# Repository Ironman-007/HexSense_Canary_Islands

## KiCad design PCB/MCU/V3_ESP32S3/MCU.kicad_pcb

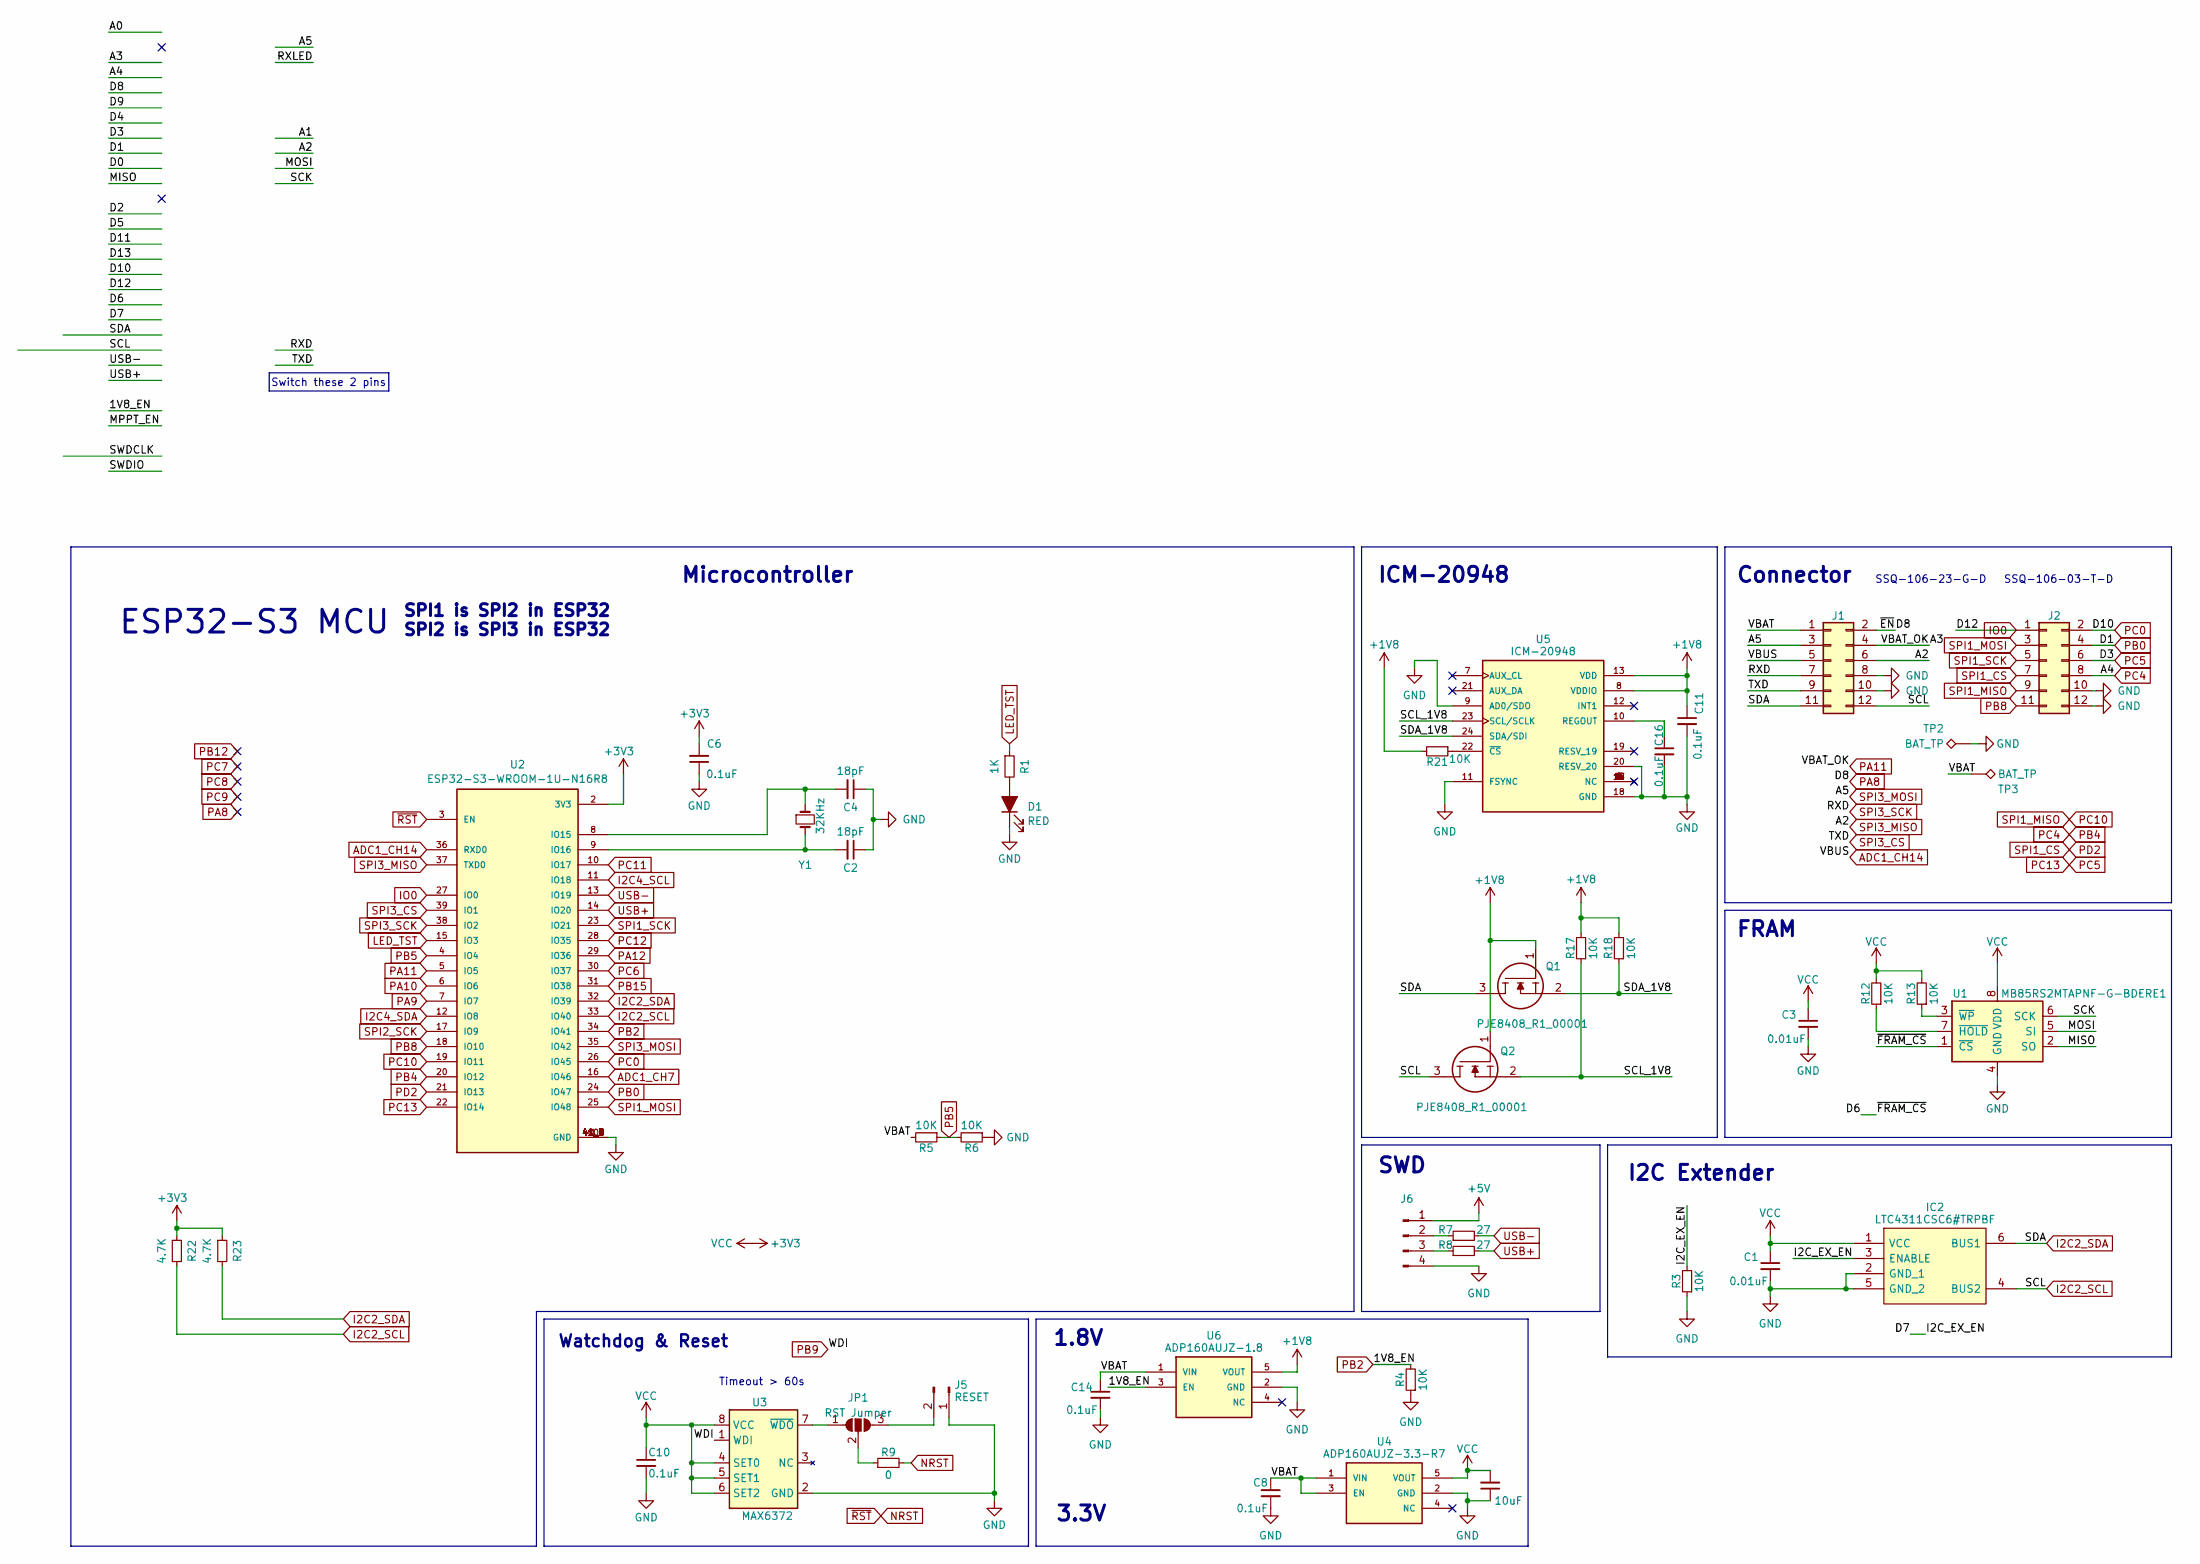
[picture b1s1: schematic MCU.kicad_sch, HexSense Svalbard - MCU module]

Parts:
C1, C3: 0.01uF; C_0402_1005Metric_Pad0.74x0.62mm_HandSolder
C2, C4: 18pF; C_0402_1005Metric_Pad0.74x0.62mm_HandSolder
C6, C8, C11, C14, C16: 0.1uF; C_0402_1005Metric_Pad0.74x0.62mm_HandSolder
C9: 10uF; C_0603_1608Metric_Pad1.08x0.95mm_HandSolder
C10: 0.1uF; C_0402_1005Metric
D1: RED; LED_0402_1005Metric_Pad0.77x0.64mm_HandSolder
IC2: LTC4311CSC6#TRPBF; SOT65P210X100-6N; Manufacturer_Part_Number LTC4311CSC6#TRPBF; Mouser Part Number 584-LTC4311CSC6TRPBF
J1, J2: Conn_02x06_Odd_Even; PinHeader_2x06_P2.54mm_Vertical
J5: RESET; PinHeader_1x02_P2.00mm_Vertical
J6: Conn_01x04_Pin; PinHeader_1x04_P2.00mm_Vertical
JP1: RST Jumper; SolderJumper-3_P1.3mm_Open_RoundedPad1.0x1.5mm
Q1, Q2: PJE8408_R1_00001; SOTFL50P160X60-3N; Manufacturer_Part_Number PJE8408_R1_00001; Mouser Part Number 241-PJE8408_R1_00001
R1: 1K; R_0402_1005Metric_Pad0.72x0.64mm_HandSolder
R3, R4, R5, R6, R12, R13, R17, R18, R21: 10K; R_0402_1005Metric_Pad0.72x0.64mm_HandSolder
R7, R8: 27; R_0402_1005Metric_Pad0.72x0.64mm_HandSolder
R9: 0; R_0201_0603Metric
R22, R23: 4.7K; R_0402_1005Metric_Pad0.72x0.64mm_HandSolder
TP2, TP3: BAT_TP; TestPoint_Pad_1.0x1.0mm
U1: MB85RS2MTAPNF-G-BDERE1; SSOP-8_5.25x5.24mm_P1.27mm
U2: ESP32-S3-WROOM-1U-N16R8; XCVR_ESP32-S3-WROOM-1U-N16R8; PARTREV v1.1
U3: MAX6372; SOT-23-8
U4: ADP160AUJZ-3.3-R7; TSOT-23-5; PARTREV H
U5: ICM-20948; InvenSense_QFN-24_3x3mm_P0.4mm; PARTREV 1.3
U6: ADP160AUJZ-1.8; TSOT-23-5; PARTREV H
Y1: 32KHz; Crystal_SMD_3215-2Pin_3.2x1.5mm

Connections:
+1V8: C11.1, Q1.1, Q2.1, R17.2, R18.2, R21.2, U5.8 (VDDIO), U5.13 (VDD), U6.5 (VOUT)
+3V3: C1.1, C3.1, C6.2, C9.2, C10.1, IC2.1 (VCC), R12.2, R13.2, R22.1, R23.1, U1.8 (VDD), U2.2 (3V3), U3.4 (SET0), U3.5 (SET1), U3.6 (SET2), U3.8 (VCC), U4.5 (VOUT)
+5V: J6.1
/D6: U1.1 (~CS)
/D7: IC2.3 (ENABLE), R3.2
/MISO: U1.2 (SO)
/MOSI: U1.5 (SI)
/SCK: U1.6 (SCK)
/SCL_1V8: Q2.2, R17.1, U5.23 (SCL/SCLK)
/SDA_1V8: Q1.2, R18.1, U5.24 (SDA/SDI)
/VBAT: C8.1, C14.1, J1.1, R5.2, TP3.1, U4.1 (VIN), U4.3 (EN), U6.1 (VIN)
ADC1_CH7: U2.16 (IO46)
ADC1_CH14: J1.5, U2.36 (RXD0)
GND: C1.2, C2.1, C3.2, C4.1, C6.1, C8.2, C9.1, C10.2, C11.2, C14.2, C16.2, D1.1 (K), IC2.2 (GND_1), IC2.5 (GND_2), J1.8, J1.10, J2.10, J2.12, J5.1, J6.4, R3.1, R4.1, R6.1, TP2.1, U1.4 (GND), U2.1 (GND), U2.40 (GND), U2.41_1 (GND), U2.41_2 (GND), U2.41_3 (GND), U2.41_4 (GND), U2.41_5 (GND), U2.41_6 (GND), U2.41_7 (GND), U2.41_8 (GND), U2.41_9 (GND), U3.2 (GND), U4.2 (GND), U5.9 (AD0/SDO), U5.11 (FSYNC), U5.18 (GND), U5.20 (RESV_20), U6.2 (GND)
I2C2_SCL: IC2.4 (BUS2), J1.12, Q2.3, R22.2, U2.33 (IO40)
I2C2_SDA: IC2.6 (BUS1), J1.11, Q1.3, R23.2, U2.32 (IO39)
I2C4_SCL: U2.11 (IO18)
I2C4_SDA: U2.12 (IO8)
IO0: J2.1, U2.27 (IO0)
LED_TST: R1.1, U2.15 (IO3)
NRST: R9.2, U2.3 (EN)
unnamed: D1.2 (A), R1.2
unnamed: J5.2, JP1.3 (B)
unnamed: J6.2, R7.1
unnamed: J6.3, R8.1
unnamed: JP1.1 (A), U3.7 (~WDO)
unnamed: JP1.2 (C), R9.1
unnamed: R12.1, U1.7 (~HOLD)
unnamed: R13.1, U1.3 (~WP)
unnamed: C4.2, U2.8 (IO15), Y1.1
unnamed: C2.2, U2.9 (IO16), Y1.2
unnamed: C16.1, U5.10 (REGOUT)
unnamed: R21.1, U5.22 (~CS)
PA8: J1.2
PA9: U2.7 (IO7)
PA10: U2.6 (IO6)
PA11: J1.4, U2.5 (IO5)
PA12: U2.29 (IO36)
PB0: J2.4, U2.24 (IO47)
PB2: R4.2, U2.34 (IO41), U6.3 (EN)
PB4: J2.8, U2.20 (IO12)
PB5: R5.1, R6.2, U2.4 (IO4)
PB8: J2.11, U2.18 (IO10)
PB9: U3.1 (WDI)
PB15: U2.31 (IO38)
PC0: J2.2, U2.26 (IO45)
PC6: U2.30 (IO37)
PC10: J2.9, U2.19 (IO11)
PC11: U2.10 (IO17)
PC12: U2.28 (IO35)
PC13: J2.6, U2.22 (IO14)
PD2: J2.7, U2.21 (IO13)
SPI1_MOSI: J2.3, U2.25 (IO48)
SPI1_SCK: J2.5, U2.23 (IO21)
SPI2_SCK: U2.17 (IO9)
SPI3_CS: J1.9, U2.39 (IO1)
SPI3_MISO: J1.6, U2.37 (TXD0)
SPI3_MOSI: J1.3, U2.35 (IO42)
SPI3_SCK: J1.7, U2.38 (IO2)
USB+: R8.2, U2.14 (IO20)
USB-: R7.2, U2.13 (IO19)

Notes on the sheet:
ICM-20948
SSQ-106-03-T-D
1.8V
SPI1 is SPI2 in ESP32 SPI2 is SPI3 in ESP32
Microcontroller
FRAM
Timeout > 60s
ESP32-S3 MCU
Watchdog & Reset
SWD
Connector
3.3V
Switch these 2 pins
SSQ-106-23-G-D
I2C Extender

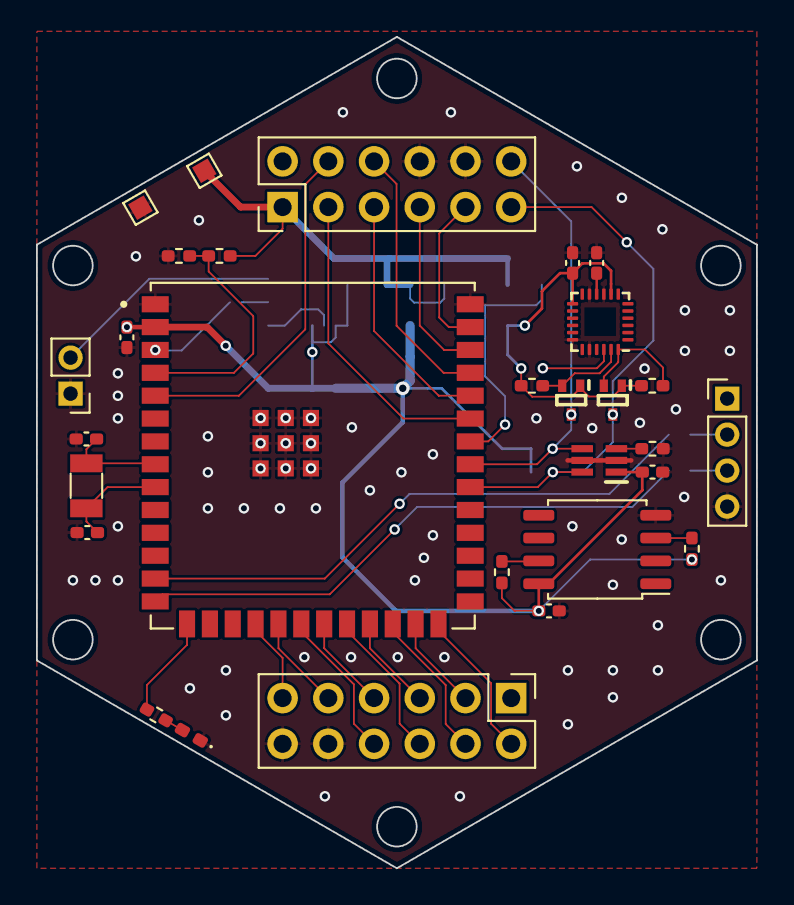
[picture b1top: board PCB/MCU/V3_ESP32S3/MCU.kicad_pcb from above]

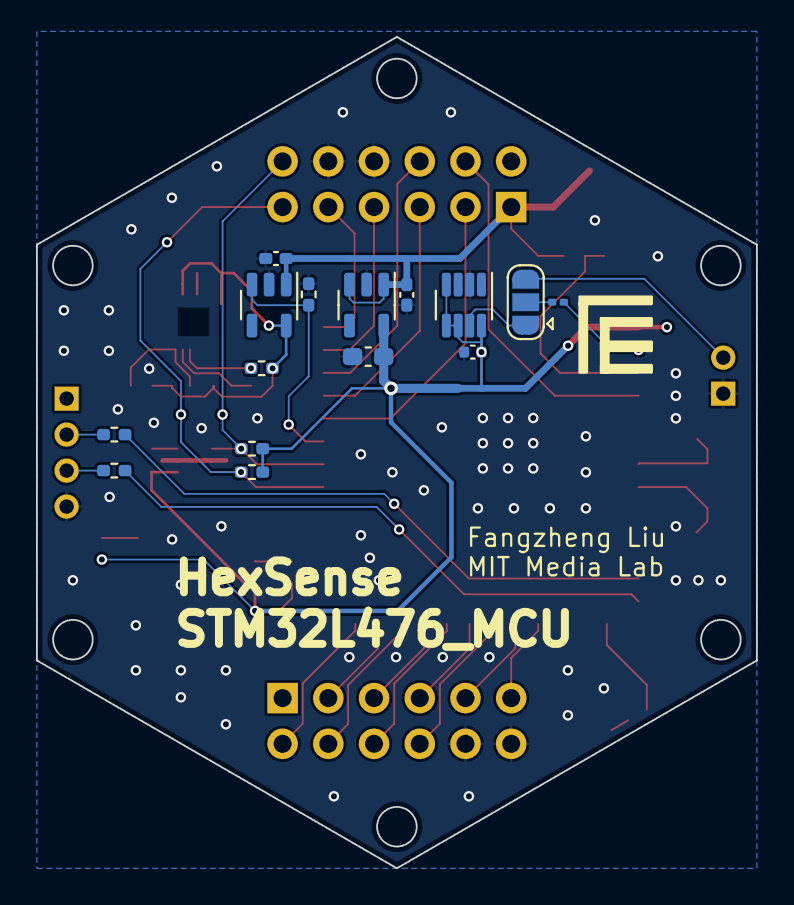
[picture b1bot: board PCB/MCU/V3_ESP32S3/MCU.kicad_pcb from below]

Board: 2 copper layers, 40.0 x 46.2 mm, 44 parts (15 on the bottom side), 43 nets.

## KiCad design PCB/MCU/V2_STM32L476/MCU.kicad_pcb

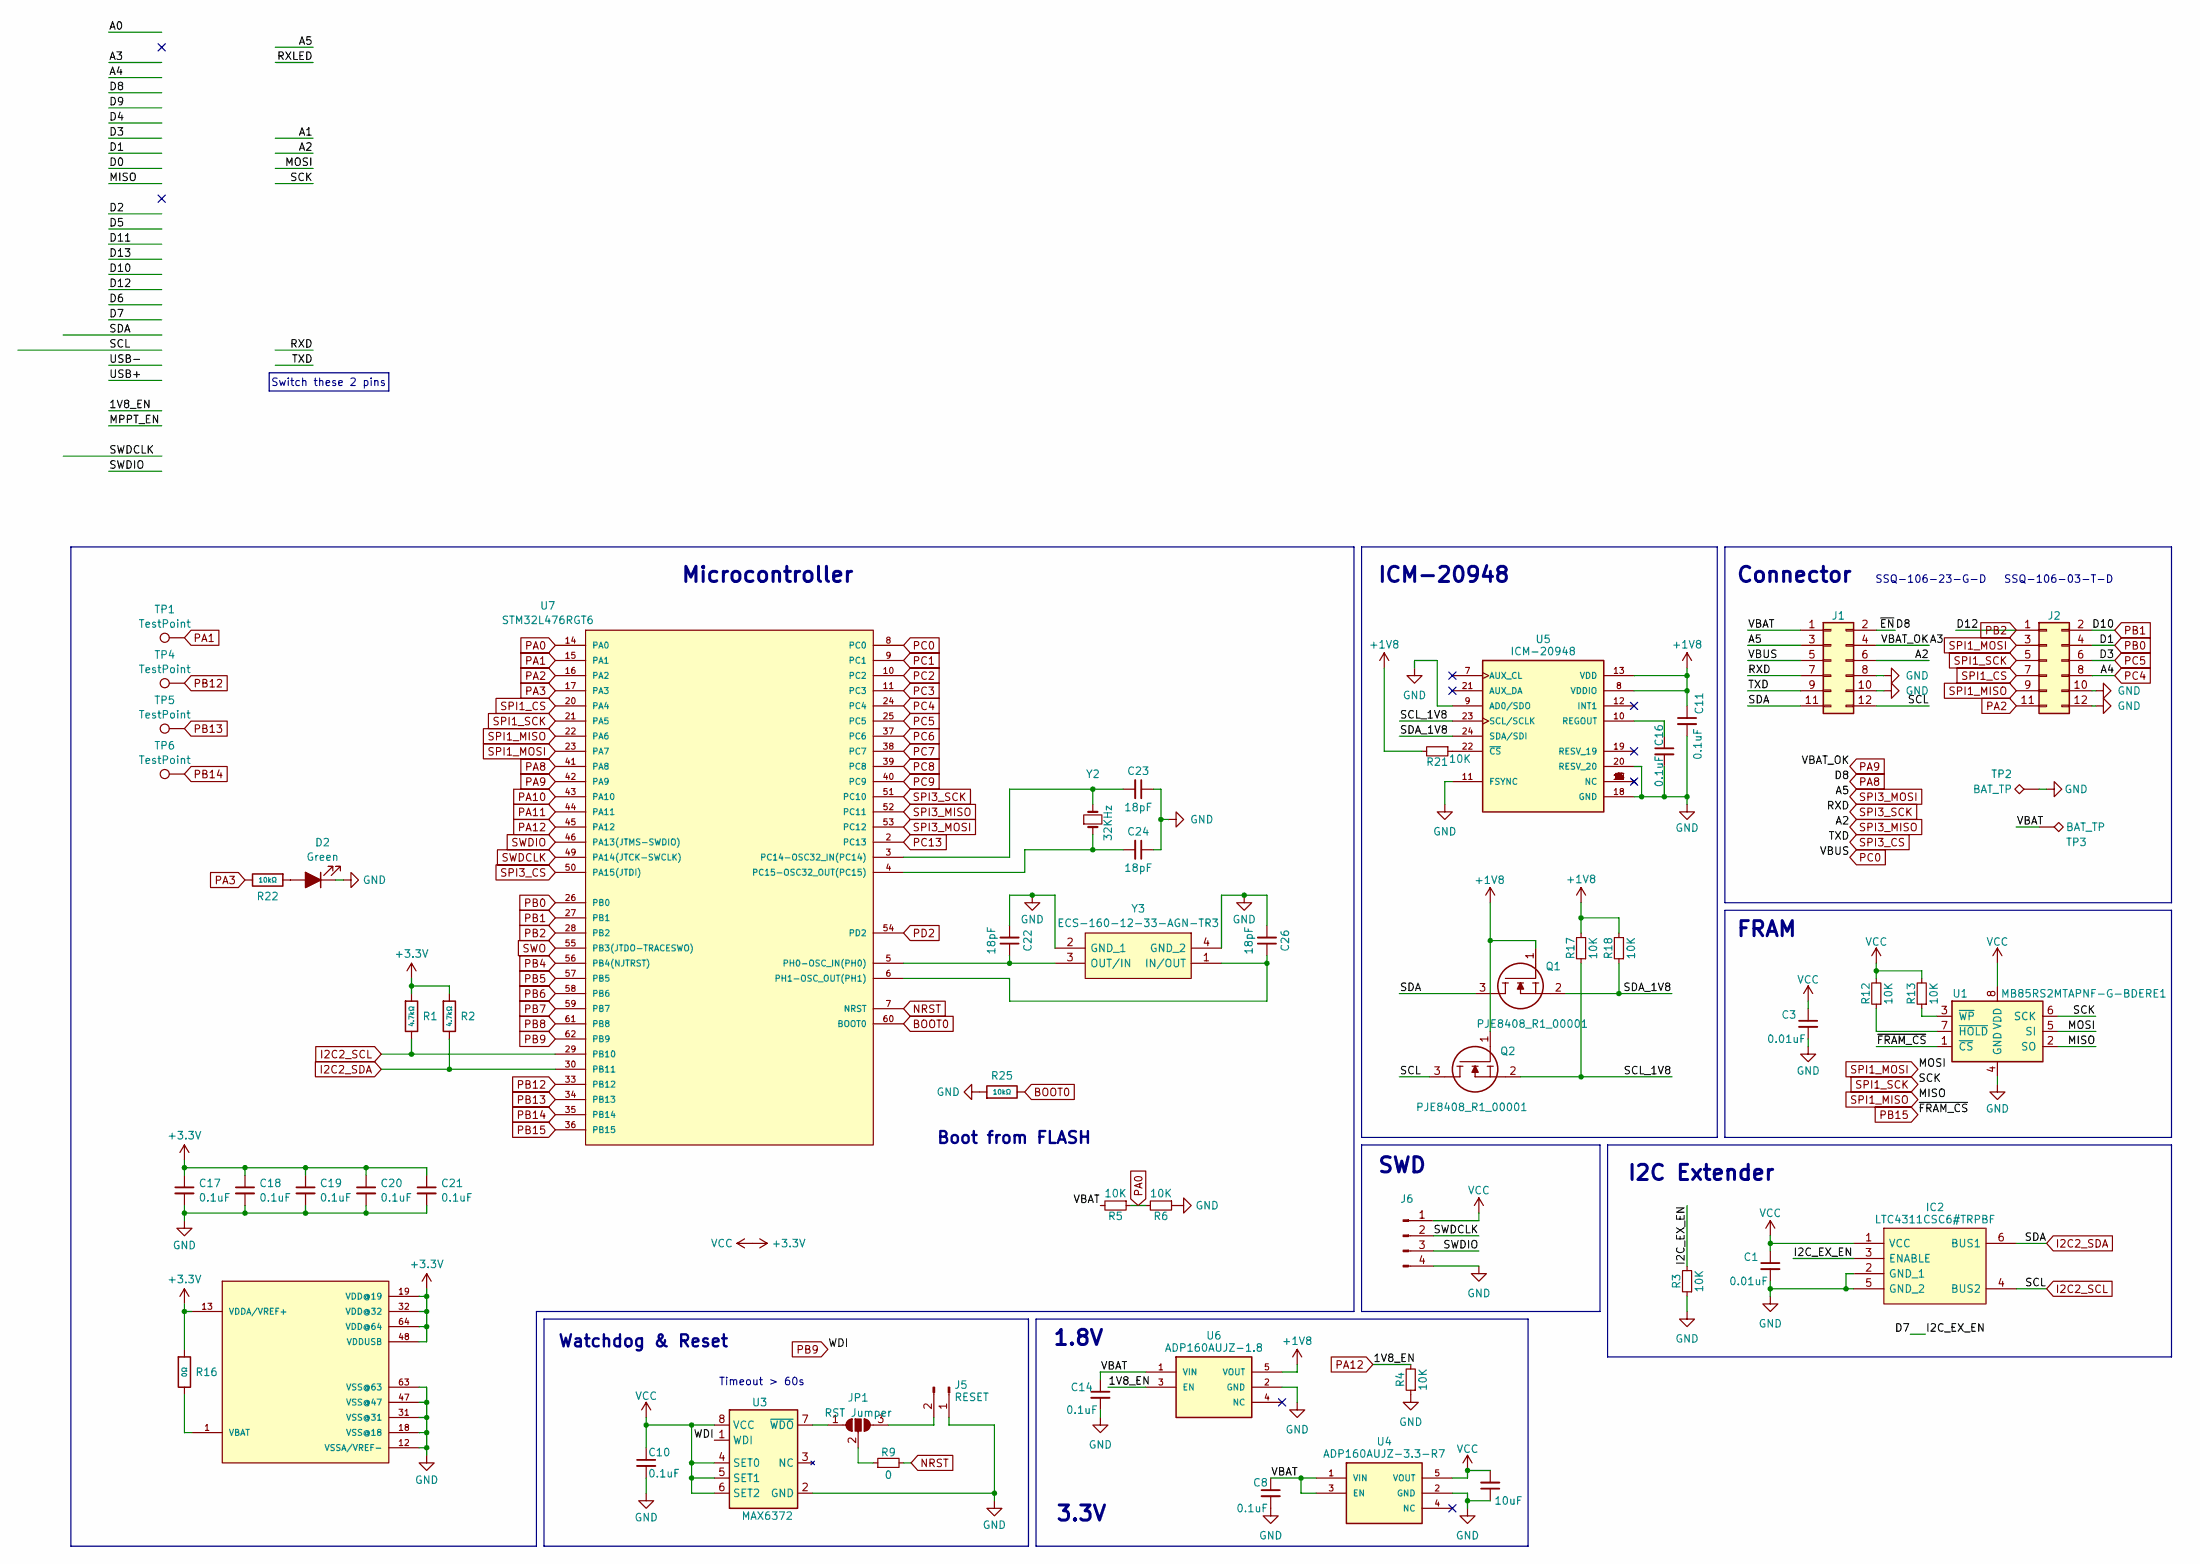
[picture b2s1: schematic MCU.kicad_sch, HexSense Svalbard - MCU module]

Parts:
C1, C3: 0.01uF; C_0402_1005Metric_Pad0.74x0.62mm_HandSolder
C8, C11, C14, C16, C17, C18, C19, C20, C21: 0.1uF; C_0402_1005Metric_Pad0.74x0.62mm_HandSolder
C9: 10uF; C_0603_1608Metric_Pad1.08x0.95mm_HandSolder
C10: 0.1uF; C_0402_1005Metric
C22, C23, C24, C26: 18pF; C_0402_1005Metric_Pad0.74x0.62mm_HandSolder
D2: Green; LED_0402_1005Metric_Pad0.77x0.64mm_HandSolder
IC2: LTC4311CSC6#TRPBF; SOT65P210X100-6N; Manufacturer_Part_Number LTC4311CSC6#TRPBF; Mouser Part Number 584-LTC4311CSC6TRPBF
J1, J2: Conn_02x06_Odd_Even; PinHeader_2x06_P2.54mm_Vertical
J5: RESET; PinHeader_1x02_P2.00mm_Vertical
J6: Conn_01x04_Pin; PinHeader_1x04_P2.00mm_Vertical
JP1: RST Jumper; SolderJumper-3_P1.3mm_Open_RoundedPad1.0x1.5mm
Q1, Q2: PJE8408_R1_00001; SOTFL50P160X60-3N; Manufacturer_Part_Number PJE8408_R1_00001; Mouser Part Number 241-PJE8408_R1_00001
R1, R2: 4.7kΩ; R_0402; Overload Voltage (Max) 50V; Tolerance ±1%; Part 0402WGF4701TCE; LCSC C25900
R3, R4, R5, R6, R12, R13, R17, R18, R21: 10K; R_0402_1005Metric_Pad0.72x0.64mm_HandSolder
R9: 0; R_0201_0603Metric
R16: 0Ω; R_0402; Overload Voltage (Max) 50V; Tolerance ±1%; Part 0402WGF0000TCE; LCSC C17168
R22: 10kΩ; R_0402_1005Metric_Pad0.72x0.64mm_HandSolder; Overload Voltage (Max) 75V; Tolerance ±1%; Part 0603WAF1001T5E; LCSC C21190
R25: 10kΩ; R_0603_1608Metric_Pad0.98x0.95mm_HandSolder; Overload Voltage (Max) 200V; Tolerance ±1%; Part 1206W4F1002T5E; LCSC C17902
TP1, TP4, TP5, TP6: TestPoint; TestPoint_Pad_D1.0mm
TP2, TP3: BAT_TP; TestPoint_Pad_1.0x1.0mm
U1: MB85RS2MTAPNF-G-BDERE1; SSOP-8_5.25x5.24mm_P1.27mm
U3: MAX6372; SOT-23-8
U4: ADP160AUJZ-3.3-R7; TSOT-23-5; PARTREV H
U5: ICM-20948; InvenSense_QFN-24_3x3mm_P0.4mm; PARTREV 1.3
U6: ADP160AUJZ-1.8; TSOT-23-5; PARTREV H
U7: STM32L476RGT6; LQFP-64_10x10mm_P0.5mm
Y2: 32KHz; Crystal_SMD_3215-2Pin_3.2x1.5mm
Y3: ECS-160-12-33-AGN-TR3; XTAL_ECS-160-12-33-AGN-TR3; Manufacturer_Part_Number ECS-160-12-33-AGN-TR3; Mouser Part Number 520-160-12-33AGN-TR3

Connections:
+1V8: C11.1, Q1.1, Q2.1, R17.2, R18.2, R21.2, U5.8 (VDDIO), U5.13 (VDD), U6.5 (VOUT)
+3.3V: C1.1, C3.1, C9.2, C10.1, C17.1, C18.1, C19.1, C20.1, C21.1, IC2.1 (VCC), J6.1, R1.1, R2.1, R12.2, R13.2, R16.1, U1.8 (VDD), U3.4 (SET0), U3.5 (SET1), U3.6 (SET2), U3.8 (VCC), U4.5 (VOUT), U7.13 (VDDA/VREF+), U7.19 (VDD@19), U7.32 (VDD@32), U7.48 (VDDUSB), U7.64 (VDD@64)
/D7: IC2.3 (ENABLE), R3.2
/SCL_1V8: Q2.2, R17.1, U5.23 (SCL/SCLK)
/SDA_1V8: Q1.2, R18.1, U5.24 (SDA/SDI)
/VBAT: C8.1, C14.1, J1.1, R5.2, TP3.1, U4.1 (VIN), U4.3 (EN), U6.1 (VIN)
BOOT0: R25.2, U7.60 (BOOT0)
GND: C1.2, C3.2, C8.2, C9.1, C10.2, C11.2, C14.2, C16.2, C17.2, C18.2, C19.2, C20.2, C21.2, C22.2, C23.1, C24.1, C26.2, D2.1 (K), IC2.2 (GND_1), IC2.5 (GND_2), J1.8, J1.10, J2.10, J2.12, J5.1, J6.4, R3.1, R4.1, R6.1, R25.1, TP2.1, U1.4 (GND), U3.2 (GND), U4.2 (GND), U5.9 (AD0/SDO), U5.11 (FSYNC), U5.18 (GND), U5.20 (RESV_20), U6.2 (GND), U7.12 (VSSA/VREF-), U7.18 (VSS@18), U7.31 (VSS@31), U7.47 (VSS@47), U7.63 (VSS@63), Y3.2 (GND_1), Y3.4 (GND_2)
I2C2_SCL: IC2.4 (BUS2), J1.12, Q2.3, R1.2, U7.29 (PB10)
I2C2_SDA: IC2.6 (BUS1), J1.11, Q1.3, R2.2, U7.30 (PB11)
NRST: R9.2, U7.7 (NRST)
unnamed: D2.2 (A), R22.1
unnamed: J5.2, JP1.3 (B)
unnamed: JP1.1 (A), U3.7 (~WDO)
unnamed: JP1.2 (C), R9.1
unnamed: R12.1, U1.7 (~HOLD)
unnamed: R13.1, U1.3 (~WP)
unnamed: C16.1, U5.10 (REGOUT)
unnamed: R21.1, U5.22 (~CS)
unnamed: C23.2, U7.3 (PC14-OSC32_IN(PC14)), Y2.2
unnamed: C24.2, U7.4 (PC15-OSC32_OUT(PC15)), Y2.1
unnamed: C22.1, U7.5 (PH0-OSC_IN(PH0)), Y3.3 (OUT/IN)
unnamed: C26.1, U7.6 (PH1-OSC_OUT(PH1)), Y3.1 (IN/OUT)
unnamed: R16.2, U7.1 (VBAT)
PA0: R5.1, R6.2, U7.14 (PA0)
PA1: TP1.1, U7.15 (PA1)
PA2: J2.11, U7.16 (PA2)
PA3: R22.2, U7.17 (PA3)
PA8: J1.2, U7.41 (PA8)
PA9: J1.4, U7.42 (PA9)
PA10: U7.43 (PA10)
PA11: U7.44 (PA11)
PA12: R4.2, U6.3 (EN), U7.45 (PA12)
PB0: J2.4, U7.26 (PB0)
PB1: J2.2, U7.27 (PB1)
PB2: J2.1, U7.28 (PB2)
PB4: U7.56 (PB4(NJTRST))
PB5: U7.57 (PB5)
PB6: U7.58 (PB6)
PB7: U7.59 (PB7)
PB8: U7.61 (PB8)
PB9: U3.1 (WDI), U7.62 (PB9)
PB12: TP4.1, U7.33 (PB12)
PB13: TP5.1, U7.34 (PB13)
PB14: TP6.1, U7.35 (PB14)
PB15: U1.1 (~CS), U7.36 (PB15)
PC0: J1.5, U7.8 (PC0)
PC1: U7.9 (PC1)
PC2: U7.10 (PC2)
PC3: U7.11 (PC3)
PC4: J2.8, U7.24 (PC4)
PC5: J2.6, U7.25 (PC5)
PC6: U7.37 (PC6)
PC7: U7.38 (PC7)
PC8: U7.39 (PC8)
PC9: U7.40 (PC9)
PC13: U7.2 (PC13)
PD2: U7.54 (PD2)
SPI1_CS: J2.7, U7.20 (PA4)
SPI1_MISO: J2.9, U1.2 (SO), U7.22 (PA6)
SPI1_MOSI: J2.3, U1.5 (SI), U7.23 (PA7)
SPI1_SCK: J2.5, U1.6 (SCK), U7.21 (PA5)
SPI3_CS: J1.9, U7.50 (PA15(JTDI))
SPI3_MISO: J1.6, U7.52 (PC11)
SPI3_MOSI: J1.3, U7.53 (PC12)
SPI3_SCK: J1.7, U7.51 (PC10)
SWDCLK: J6.2, U7.49 (PA14(JTCK-SWCLK))
SWDIO: J6.3, U7.46 (PA13(JTMS-SWDIO))
SWO: U7.55 (PB3(JTDO-TRACESWO))

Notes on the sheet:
ICM-20948
SSQ-106-03-T-D
1.8V
Microcontroller
FRAM
Timeout > 60s
Watchdog & Reset
SWD
Connector
3.3V
Boot from FLASH
Switch these 2 pins
SSQ-106-23-G-D
I2C Extender

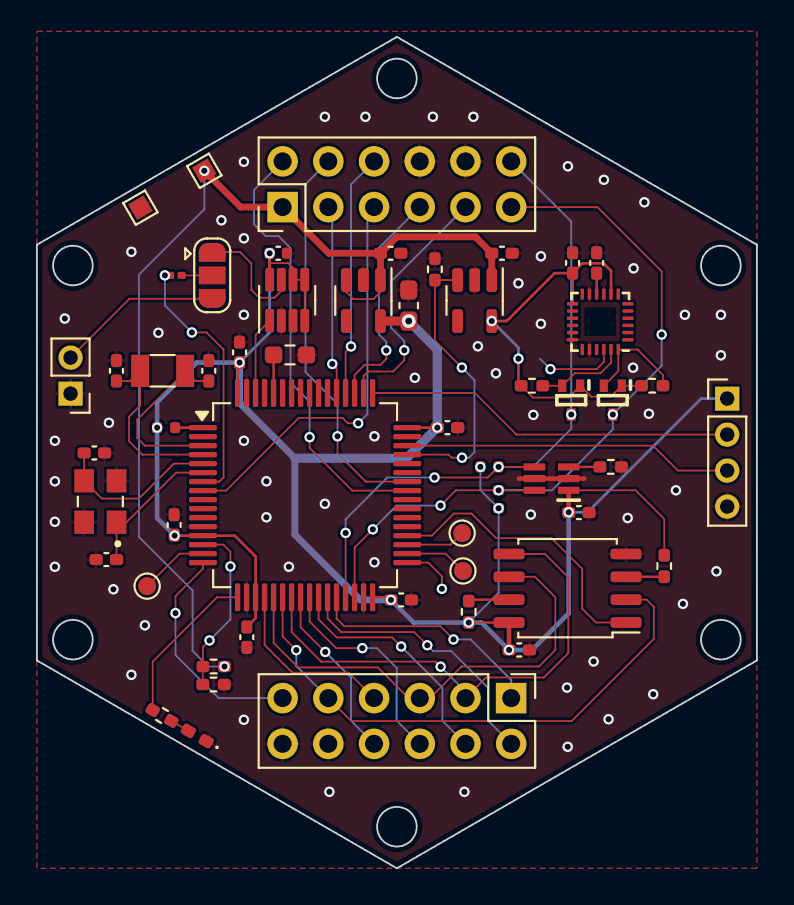
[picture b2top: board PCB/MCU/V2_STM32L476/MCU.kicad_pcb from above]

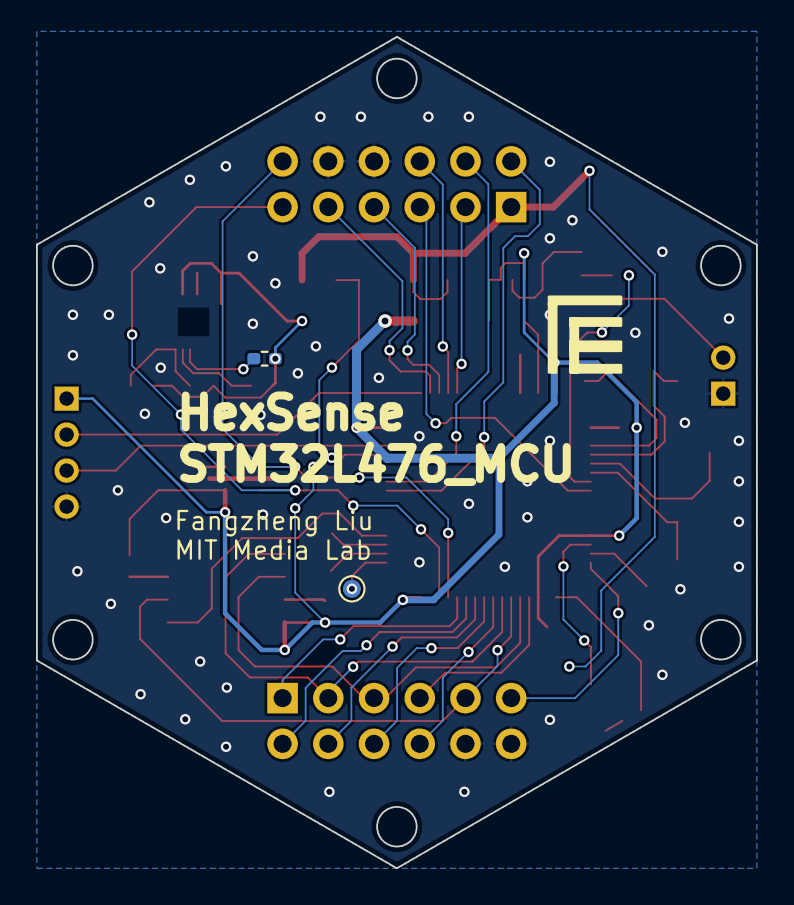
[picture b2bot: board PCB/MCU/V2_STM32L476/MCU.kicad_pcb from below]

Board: 2 copper layers, 40.0 x 46.2 mm, 55 parts (2 on the bottom side), 52 nets.

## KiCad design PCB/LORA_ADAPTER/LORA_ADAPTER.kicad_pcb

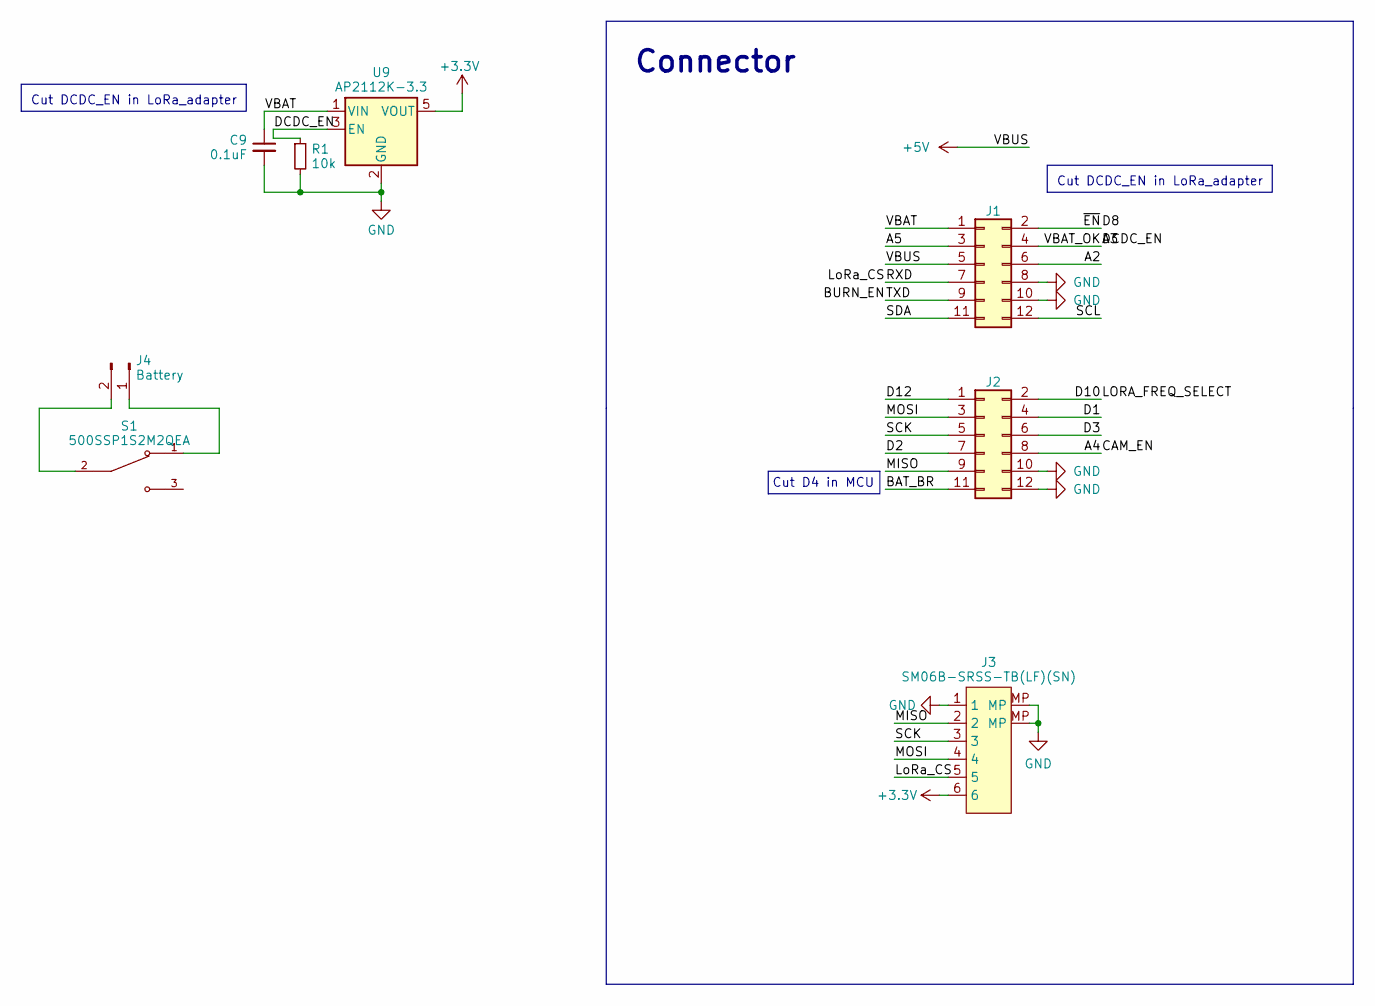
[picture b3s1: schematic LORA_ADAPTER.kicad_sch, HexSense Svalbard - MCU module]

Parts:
C9: 0.1uF; C_0402_1005Metric_Pad0.74x0.62mm_HandSolder
J1, J2: Conn_02x06_Odd_Even; PinHeader_2x06_P2.54mm_Vertical
J3: SM06B-SRSS-TB(LF)(SN); JST_SH_SM06B-SRSS-TB_1x06-1MP_P1.00mm_Horizontal
J4: Battery; PinHeader_1x02_P2.54mm_Vertical
R1: 10k; R_0402_1005Metric_Pad0.72x0.64mm_HandSolder
S1: 500SSP1S2M2QEA; SW_500SSP1S2M2QEA; PARTREV C
U9: AP2112K-3.3; SOT-23-5

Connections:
+3V3: J3.6, U9.5 (VOUT)
+5V: J1.5
/A2: J1.6
/A3: J1.4, R1.1, U9.3 (EN)
/A4: J2.8
/A5: J1.3
/BAT_BR: J2.11
/BURN_EN: J1.9
/D1: J2.4
/D2: J2.7
/D3: J2.6
/D8: J1.2
/D10: J2.2
/D12: J2.1
/LoRa_CS: J1.7, J3.5
/MISO: J2.9, J3.2
/MOSI: J2.3, J3.4
/SCK: J2.5, J3.3
/SCL: J1.12
/SDA: J1.11
/VBAT: C9.1, J1.1, U9.1 (VIN)
GND: C9.2, J1.8, J1.10, J2.10, J2.12, J3.1, J3.MP, R1.2, U9.2 (GND)
unnamed: J4.1, S1.1
unnamed: J4.2, S1.2

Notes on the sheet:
Cut D4 in MCU
Connector
Cut DCDC_EN in LoRa_adapter

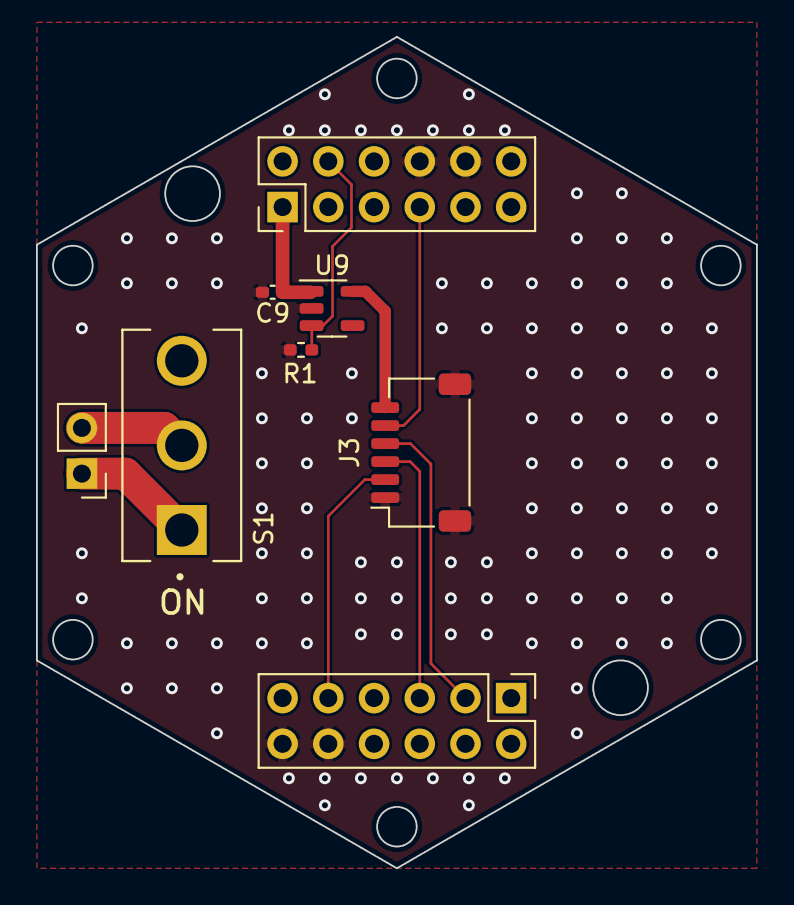
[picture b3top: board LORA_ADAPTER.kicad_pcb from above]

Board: 2 copper layers, 40.0 x 46.2 mm, 8 parts (0 on the bottom side), 10 nets.

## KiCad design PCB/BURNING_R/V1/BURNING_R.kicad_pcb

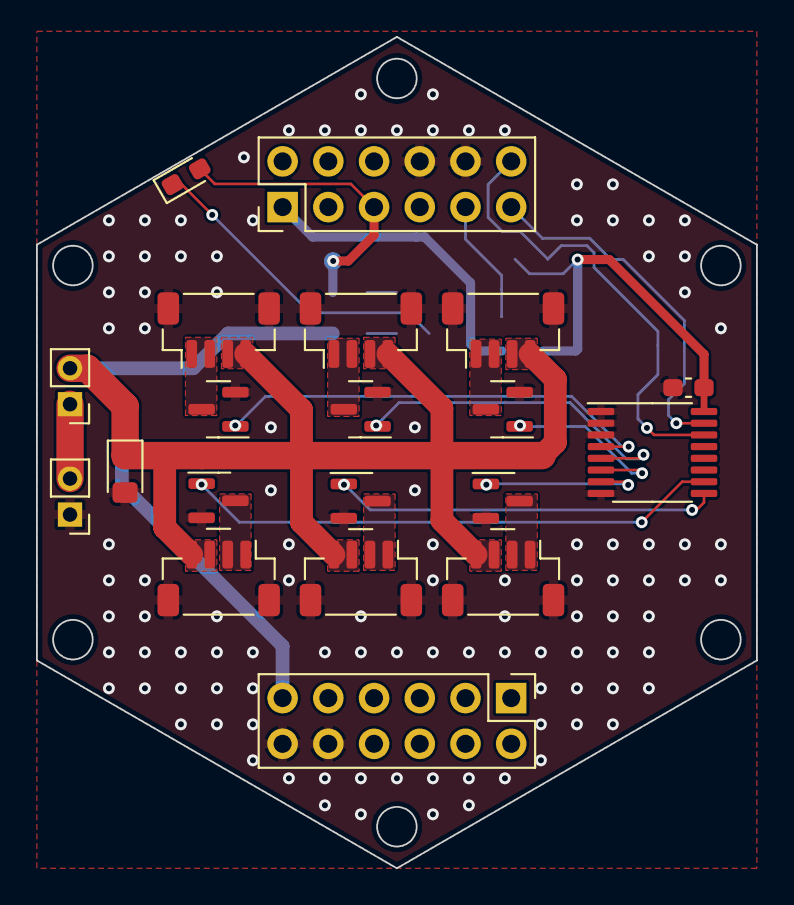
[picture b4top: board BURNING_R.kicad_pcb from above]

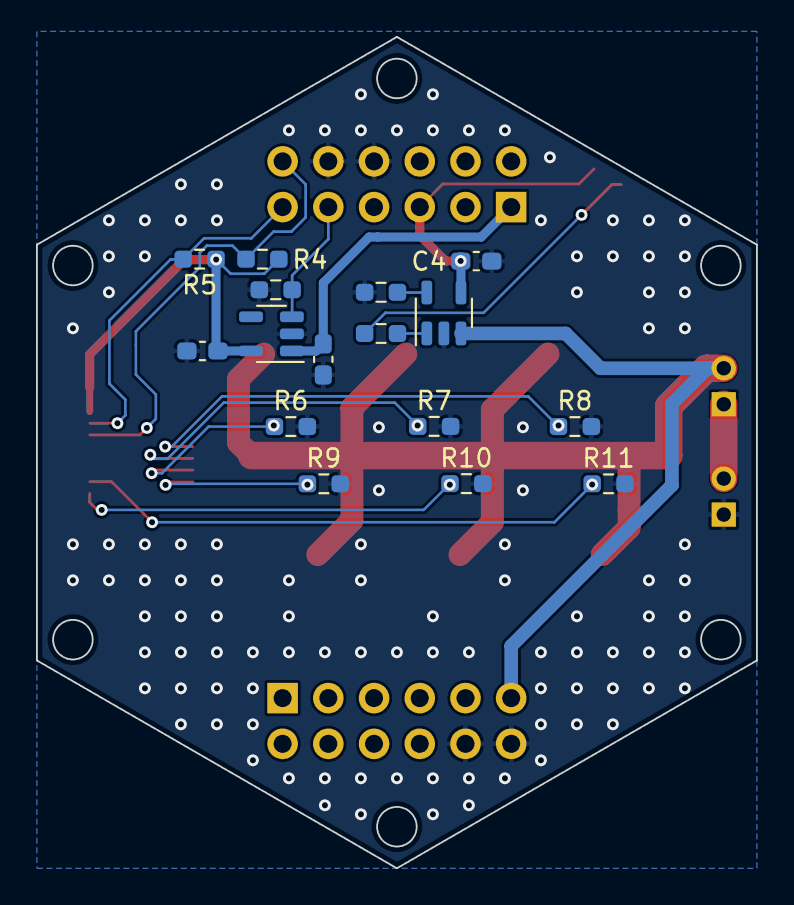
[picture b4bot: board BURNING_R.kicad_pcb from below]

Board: 2 copper layers, 40.0 x 46.2 mm, 36 parts (16 on the bottom side), 24 nets.

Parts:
C2, C4, C6: 0.1uF; C_0603_1608Metric_Pad1.08x0.95mm_HandSolder
C3: 47uF; LED_0805_2012Metric_Pad1.15x1.40mm_HandSolder
C5: 10uF; C_0603_1608Metric_Pad1.08x0.95mm_HandSolder
D1: RED; LED_0603_1608Metric_Pad1.05x0.95mm_HandSolder
J1, J2: Conn_02x06_Odd_Even; PinHeader_2x06_P2.54mm_Vertical
J3, J4, J5, J6, J7, J8: BR_conn; JST_SH_BM04B-SRSS-TB_1x04-1MP_P1.00mm_Vertical
J9: Battery; PinHeader_1x02_P2.00mm_Vertical
J10: Switch; PinHeader_1x02_P2.00mm_Vertical
Q1, Q2, Q3, Q4, Q5, Q6: DMN2056U; SOT-23
R1, R2, R3: 1k; R_0603_1608Metric_Pad0.98x0.95mm_HandSolder
R4, R5: NC; R_0603_1608Metric_Pad0.98x0.95mm_HandSolder
R6, R7, R8, R9, R10, R11: 10k; R_0603_1608Metric_Pad0.98x0.95mm_HandSolder
U1: TCA9534; TSSOP-16_4.4x5mm_P0.65mm
U2: MCP73831-2-OT; SOT-23-5
U3: ADP160AUJZ-3.3-R7; TSOT-23-5

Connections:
+5V: C4.1, D1.2 (A), J1.5, U2.4 (VDD)
/BAT_BR: C3.1, J2.11, J3.3, J3.4, J4.3, J4.4, J5.3, J5.4, J6.3, J6.4, J7.3, J7.4, J8.3, J8.4, J9.2, U2.3 (VBAT)
/BR_1: J3.1, J3.2, Q1.3 (D)
/BR_1_EN: Q1.1 (G), R11.1, U1.10 (P5)
/BR_2: J4.1, J4.2, Q2.3 (D)
/BR_2_EN: Q2.1 (G), R10.1, U1.9 (P4)
/BR_3: J5.1, J5.2, Q3.3 (D)
/BR_3_EN: Q3.1 (G), R9.1, U1.7 (P3)
/BR_4: J6.1, J6.2, Q4.3 (D)
/BR_4_EN: Q4.1 (G), R8.1, U1.4 (P0)
/BR_5: J7.1, J7.2, Q5.3 (D)
/BR_5_EN: Q5.1 (G), R7.1, U1.5 (P1)
/BR_6: J8.1, J8.2, Q6.3 (D)
/BR_6_EN: Q6.1 (G), R6.1, U1.6 (P2)
/BURN_EN: J1.9, R3.2, U3.3 (EN)
/SCL: J1.12, R4.2, U1.14 (SCL)
/SDA: J1.11, R5.2, U1.15 (SDA)
/VBAT: C6.1, J1.1, U3.1 (VIN)
GND: C2.2, C3.2, C4.2, C5.1, C6.2, J1.8, J1.10, J2.10, J2.12, J3.MP, J4.MP, J5.MP, J6.MP, J7.MP, J8.MP, J10.1, Q1.2 (S), Q2.2 (S), Q3.2 (S), Q4.2 (S), Q5.2 (S), Q6.2 (S), R1.1, R3.1, R6.2, R7.2, R8.2, R9.2, R10.2, R11.2, U1.1 (A0), U1.2 (A1), U1.3 (A2), U1.8 (GND), U2.2 (VSS), U3.2 (GND)
unnamed: D1.1 (K), R2.2
unnamed: J9.1, J10.2
unnamed: R1.2, U2.5 (PROG)
unnamed: R2.1, U2.1 (STAT)
VCC: C2.1, C5.2, R4.1, R5.1, U1.16 (VDD), U3.5 (VOUT)

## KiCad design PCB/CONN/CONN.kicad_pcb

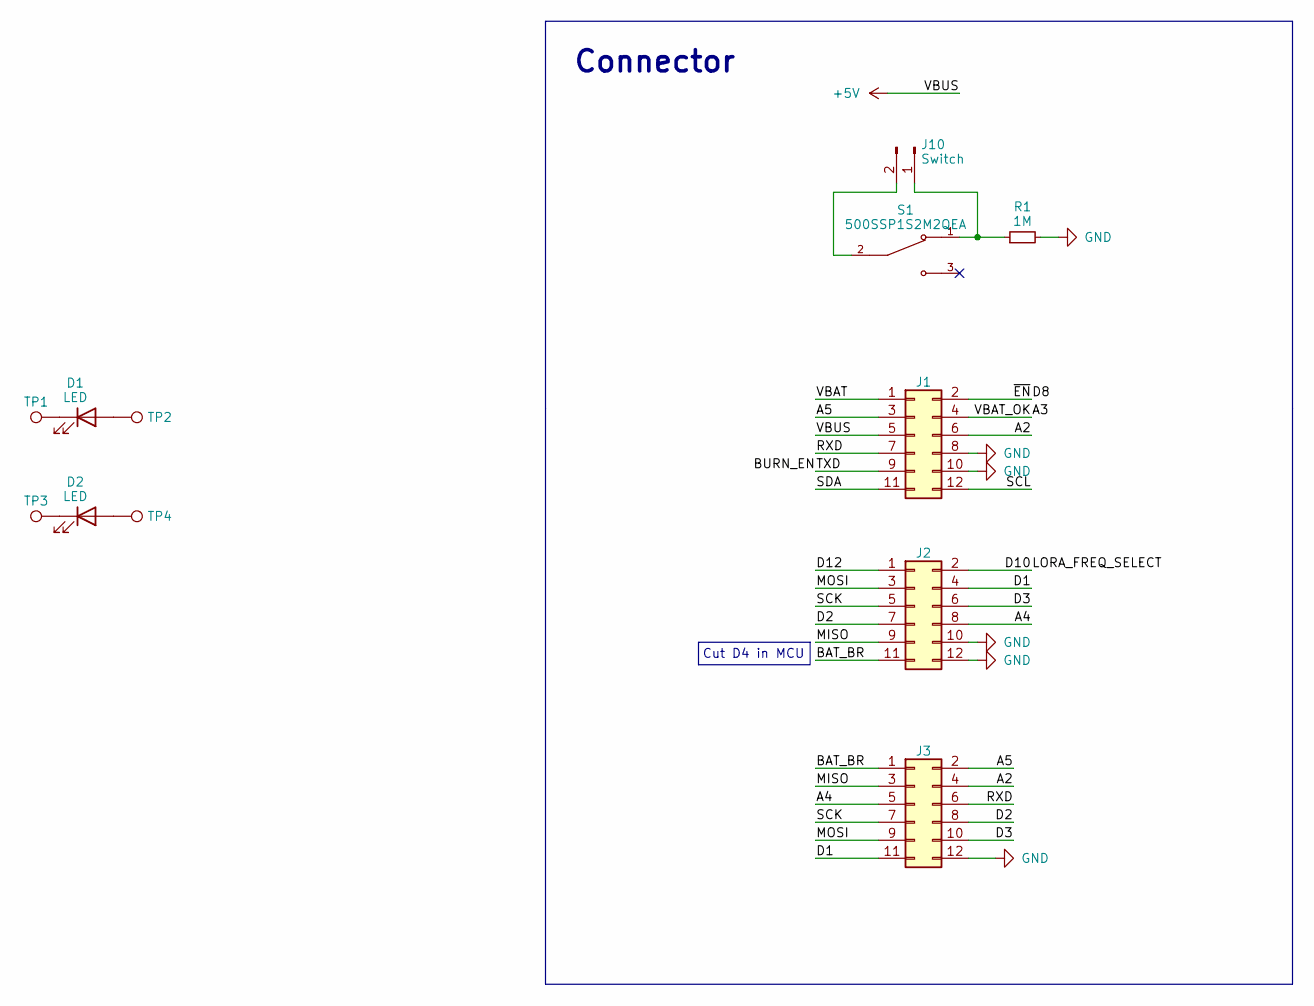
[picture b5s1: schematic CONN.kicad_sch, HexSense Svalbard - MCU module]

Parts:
D1, D2: LED; LED_1206_3216Metric_Pad1.42x1.75mm_HandSolder
J1, J2, J3: Conn_02x06_Odd_Even; PinHeader_2x06_P2.54mm_Vertical
J10: Switch; PinHeader_1x02_P2.00mm_Vertical
R1: 1M; R_0603_1608Metric_Pad0.98x0.95mm_HandSolder
S1: 500SSP1S2M2QEA; SW_500SSP1S2M2QEA; PARTREV C
TP1, TP2, TP3, TP4: TestPoint; TestPoint_Pad_1.0x1.0mm

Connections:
+5V: J1.5
/A2: J1.6, J3.4
/A3: J1.4
/A4: J2.8, J3.5
/A5: J1.3, J3.2
/BAT_BR: J2.11, J3.1
/BURN_EN: J1.9
/D1: J2.4, J3.11
/D2: J2.7, J3.8
/D3: J2.6, J3.10
/D8: J1.2
/D10: J2.2
/D12: J2.1
/MISO: J2.9, J3.3
/MOSI: J2.3, J3.9
/RXD: J1.7, J3.6
/SCK: J2.5, J3.7
/SCL: J1.12
/SDA: J1.11
/VBAT: J1.1
GND: J1.8, J1.10, J2.10, J2.12, J3.12, R1.2
unnamed: D1.2 (A), TP2.1
unnamed: D1.1 (K), TP1.1
unnamed: D2.2 (A), TP4.1
unnamed: D2.1 (K), TP3.1
unnamed: J10.1, R1.1, S1.1
unnamed: J10.2, S1.2

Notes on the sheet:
Connector
Cut D4 in MCU
